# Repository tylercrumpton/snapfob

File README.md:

# SNAPfob
SNAPfob is Synapse SM220-powered keyfob for interacting with SNAP networks. The current version has four buttons
and is designed to fit inside a [Polycase FB-45 keyfob enclosure](http://www.polycase.com/fb-45). The SNAPfob runs off of a single CR2032
and should be in a low-power sleep mode until a button press triggers an interrupt.

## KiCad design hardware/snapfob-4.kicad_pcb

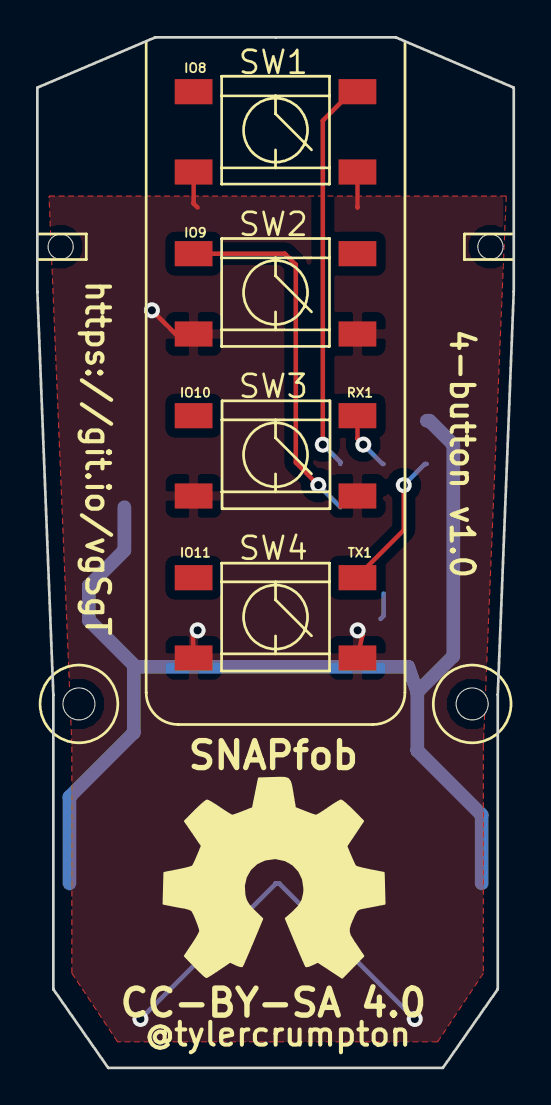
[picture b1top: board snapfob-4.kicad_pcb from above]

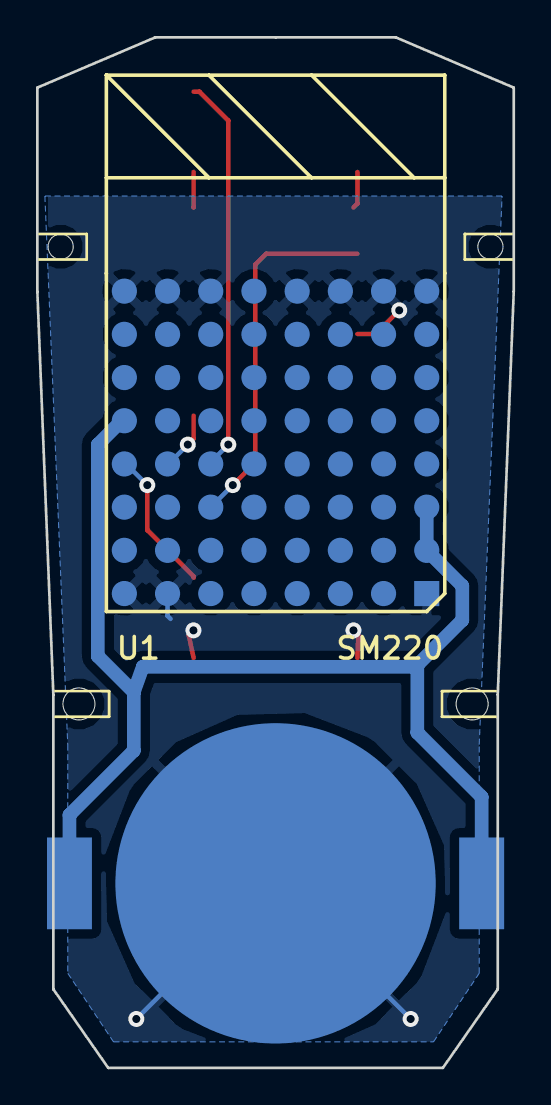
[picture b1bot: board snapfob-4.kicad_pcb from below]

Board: 2 copper layers, 26.5 x 57.3 mm, 7 parts (2 on the bottom side), 6 nets.

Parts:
BT1: BATTERY; CR2032_HOLDER
FB-45: VAL**; FB-45-4
SW1: SW1; 6x6mm_pushbutton_smd
SW2: SW2; 6x6mm_pushbutton_smd
SW3: SW3; 6x6mm_pushbutton_smd
SW4: SW4; 6x6mm_pushbutton_smd
U1: SM220; SM200

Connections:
+3.3V: BT1.1, U1.A2, U1.A3, U1.H5
GND: BT1.2, SW1.2, SW2.2, SW3.2, SW4.2, U1.A1, U1.A8, U1.B8, U1.C8, U1.D8, U1.F8, U1.G1, U1.G8, U1.H1, U1.H8
unnamed: SW1.1, U1.F4
unnamed: SW2.1, U1.F3
unnamed: SW3.1, U1.G4
unnamed: SW4.1, U1.H4

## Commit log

2016-02-14 Initial project setup.
2016-02-14 Add schematic capture.
2016-02-14 Create initial PCB part layout.
2016-02-15 First attempt at routing.
2016-02-15 Pull CLKI low per datasheet.
2016-02-15 Add some silk for IO designations.
2016-02-15 Create README.md file.

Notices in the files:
hardware/snapfob-4.kicad_pcb:
CC-BY-SA 4.0
